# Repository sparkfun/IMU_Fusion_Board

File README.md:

SparkFun IMU Fusion Board - ADXL345 & IMU3000
========================================

[*SparkFun IMU Fusion Board - ADXL345 & IMU3000 (SEN-10252)*](https://www.sparkfun.com/products/10252)

The IMU 3000 breakout features a 3-axis MEMS digital gyro with programmable ranges from +-250 to +-2000 degrees/sec. 
In addition, it has a secondary I2C port that interfaces with a digital accelerometer to deliver a complete 6-axis sensor output from its primary I2C port. 
The fusion output offloads the intensive motion processing computation requirements from the host processor, reducing the need for frequent polling of the motion sensor output and enabling low cost, low power microcontrollers.

Repository Contents
-------------------
* **/Hardware** - Eagle design files (.brd, .sch)
* **/Production** - Production panel files (.brd)

Documentation
--------------
* **[SparkFun Fritzing repo](https://github.com/sparkfun/Fritzing_Parts)** - Fritzing diagrams for SparkFun products.
* **[SparkFun 3D Model repo](https://github.com/sparkfun/3D_Models)** - 3D models of SparkFun products. 

License Information
-------------------
This product is _**open source**_! 

The **hardware** is released under [Creative Commons ShareAlike 4.0 International](https://creativecommons.org/licenses/by-sa/4.0/).

Please use, reuse, and modify these files as you see fit. Please maintain attribution to SparkFun Electronics and release anything derivative under the same license.

Distributed as-is; no warranty is given.

- Your friends at SparkFun.

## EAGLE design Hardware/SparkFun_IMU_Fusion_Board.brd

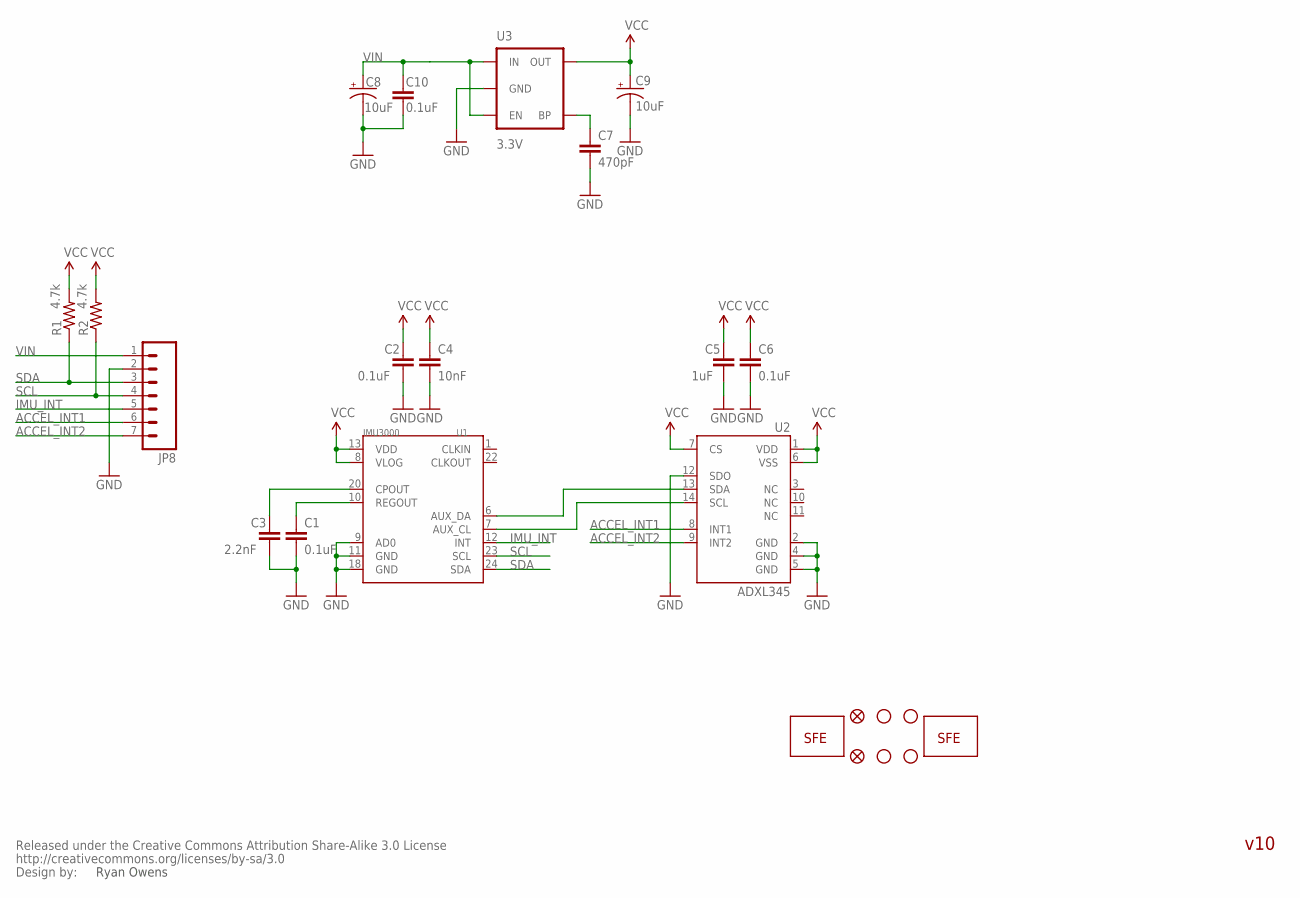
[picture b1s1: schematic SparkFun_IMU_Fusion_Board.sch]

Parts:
C1, C2, C6, C10: 0.1uF; 0603-CAP
C3: 2.2nF; 0603-CAP
C4: 10nF; 0603-CAP
C5: 1uF; 0603-CAP
C7: 470pF; 0603-CAP
C8, C9: 10uF; EIA3216
JP1: LOGO-SFENEW; SFE-NEW-WEBLOGO
JP2, JP3: FIDUCIAL1X2; FIDUCIAL-1X2
JP4, JP5, JP6, JP7: STAND-OFF
JP8: M07; 1X07
JP9: LOGO-SFESK; SFE-LOGO-FLAME
R1, R2: 4.7k; 0603-RES
U1: IMU3000; QFN-24
U2: ADXL345; LGA14
U3: 3.3V; SOT23-5
U$1: CREATIVE_COMMONS

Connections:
ACCEL_INT1: JP8.6, U2.8 (INT1)
ACCEL_INT2: JP8.7, U2.9 (INT2)
GND: C1.2, C2.2, C3.2, C4.2, C5.2, C6.2, C7.2, C8.C (-), C9.C (-), C10.2, JP8.2, U1.9 (AD0), U1.11 (GND), U1.18 (GND), U2.2 (GND), U2.4 (GND), U2.5 (GND), U2.12 (SDO), U3.2 (GND)
IMU_INT: JP8.5, U1.12 (INT)
unnamed: U1.6 (AUX_DA), U2.13 (SDA)
unnamed: C3.1, U1.20 (CPOUT)
unnamed: U1.7 (AUX_CL), U2.14 (SCL)
unnamed: C1.1, U1.10 (REGOUT)
unnamed: C7.1, U3.4 (BP)
SCL: JP8.4, R2.1, U1.23 (SCL)
SDA: JP8.3, R1.1, U1.24 (SDA)
VCC: C2.1, C4.1, C5.1, C6.1, C9.A (+), R1.2, R2.2, U1.8 (VLOG), U1.13 (VDD), U2.1 (VDD), U2.6 (VSS), U2.7 (CS), U3.5 (OUT)
VIN: C8.A (+), C10.1, JP8.1, U3.1 (IN), U3.3 (EN)

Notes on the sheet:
Ryan Owens
v10

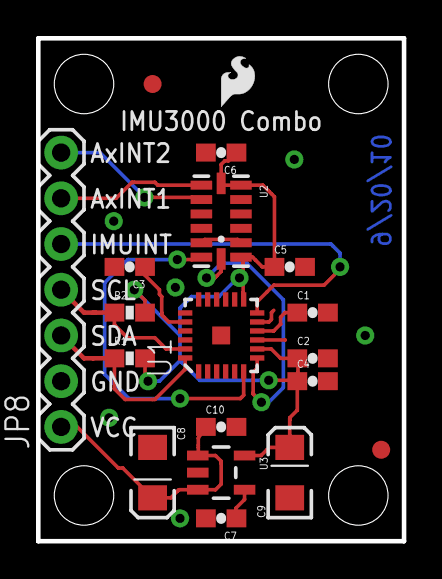
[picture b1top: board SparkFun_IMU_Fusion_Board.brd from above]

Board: 2 copper layers, 20.3 x 27.9 mm, 25 parts (1 on the bottom side), 13 nets.

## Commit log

2015-05-07 Adding hardware files

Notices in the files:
parts and their libraries:
SparkFun: Released under the Creative Commons Attribution Share-Alike 3.0 License
SparkFun: http://creativecommons.org/licenses/by-sa/3.0
